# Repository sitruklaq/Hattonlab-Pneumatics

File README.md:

# 1. Overview
This system is designed to control multi-channel pneumatic smart surfaces using only small amounts of air. The pneumatic system consists of 8 independent pneumatic channels that can access positive, negative, and neutral (exhaust) states. For a smaller, portable setup, please refer to this respository: https://github.com/sitruklaq/Mini-Pneumatics

## 1.1 Table of Contents
* [1\. Overview](#1-overview)
  * [1\.1 Table of Contents](#11-table-of-contents)
* [2\. Components &amp; Pneumatic Logic](#2-components--pneumatic-logic)
* [3\. Instrument Control](#3-instrument-control)
  * [3\.1 Serial Command List](#31-serial-command-list)
    * [3\.1\.1 Valve Control](#311-valve-control)
    * [3\.1\.2 Reservoir Setpoints](#312-reservoir-setpoints)
    * [3\.1\.3 Pressure Readings](#313-pressure-readings)
* [4\. Visual Control App](#4-visual-control-app)
* [5\. Setpoint Pressure Control](#5-setpoint-pressure-control)
* [6\. Electrical Circuitry](#6-electrical-circuitry)
  * [6\.1 Electrical Components](#61-electrical-components)
  * [6\.2 PCBs](#62-pcbs)
    * [6\.2\.2 Input Valve PCB](#622-input-valve-pcb)
    * [6\.2\.3 Output Valve PCB](#623-output-valve-pcb)
    * [6\.2\.4 2 Sensor Board](#624-2-sensor-board)
[TOC]
# 2. Components & Pneumatic Logic

The instrument is designed to provide 3 pressure 'input' states: positive (+∆P), negative, (-∆P), and neutral (0∆P). Postive and negative pressures are generated through pneumatic pumps and held in reservoirs. The pressure for each reservoir is defined by the user and monitored through in-line pressure sensors. Pneumatic valves can be toggled to open and enter a common pressure line which can be accessed by independent valves that lead to channels (N=8). 

The valves are rated for +-100kPa while the pumps are generally able to reach ~+-60kPa. Valve response time is <5ms.

# 3. Instrument Control

An Arduino microncontroller is responsible for opening and closing the pneumatic valves in addition to regulating pressure setpoints of the reservoirs. 

This instrument is controlled through a Serial Connection to a computer. 

Communication to the microcontroller is accomplished through serial communication. Commands for valve control, setpoint, and pressure value requests are available in the X section.

A MATLAB GUI app uses these commands to visually control the pneumatics.

screenshot to be added later.

## 3.1 Serial Command List

The Arduino is listening for serial commands in the following structure ‘< command, optional modifier, optional modifier>’.

### 3.1.1 Valve Control

| Command Syntax | Description                                                  | Example                                 |
| :------------: | ------------------------------------------------------------ | --------------------------------------- |
|     **VO**     | **VALVE OUTPUT** Changes the state of a single output valve. <command, valve # (0-7), valve state (0-closed 1-open)> | <VO, 4, 1> opens the fifth output valve |
|     **VI**     | **VALVE INPUT**Changes the state of a single input valve. <command, valve # (0-7), valve state (0-off 1-on)> | <VO, 4, 1> opens the fifth output valve |
|    **AIV**     | **ALL INPUT VALVES** Changes the state of all input valves <command, 0/1> | <AIV,1> opens all input valves          |
|    **AOV**     | **ALL OUTPUT VALVES** Changes the state of all outpu valves <command, 0/1> | <AOV, 0> turns off all output valves    |

### 3.1.2 Reservoir Setpoints

| Command Syntax | Description                                                  | Example    |
| :------------: | ------------------------------------------------------------ | ---------- |
|    **PSP**     | Changes setpoint of positive pressure reservoir              | <PSP, 15>  |
|    **NSP**     | Changes setpoint of negative pressure reservoir              | <NSP, -15> |
|    **PVN**     | **PRESSURE VALUE NEGATIVE** prints the pressure value of the negative pressure reservoir | <PVN>      |
|    **PVO**     | **PRESSURE VALUE OUTPUT** prints the pressure value of an output pressure channel | <PVO, 3>   |
|    **PVP**     | **PRESSURE VALUE POSITIVE** prints the pressure value of the positive pressure reservoir | <PVP>      |

### 3.1.3 Pressure Readings

| Command Syntax | Description                                                  | Example  |
| :------------: | ------------------------------------------------------------ | :------: |
|      PVP       | **PRESSURE VALUE POSITIVE** prints the pressure value of the positive pressure reservoir |  <PVP>   |
|      PVN       | **PRESSURE VALUE NEGATIVE** prints the pressure value of the negative pressure reservoir |  <PVN>   |
|      PVO       | **PRESSURE VALUE OUTPUT** prints the pressure value of an output pressure channel | <PVO, 3> |

# 4. Visual Control App

A visual control app was designed using Matlab App Designer. The app is basic in functionality but is able to control valves through sending serial commands. 

# 5. Setpoint Pressure Control

Reservoir pressure is controlled by simple state monitoring. The pressure sensors monitor the pressure and the pump is turned on if the pressure drops below the Setpoint (with a small threshold).

# 6. Electrical Circuitry

## 6.1 Electrical Components

Power is supplied by an off board 12V 5A brick-style switching power supply. The 12V power is then split and one side is stepped down to 5V. The valves run on the 5V rail and are toggled through npn transistors powered by an Arduino.

**12V**

- Pumps
- Motor Controller

**5V**

- Valves

**5V (Computer-> Arduino)**

- pressure sensors
- transistors
- leds

## 6.2 PCBs

### 6.2.2 Input Valve PCB

### 6.2.3 Output Valve PCB

### 6.2.4 2 Sensor Board

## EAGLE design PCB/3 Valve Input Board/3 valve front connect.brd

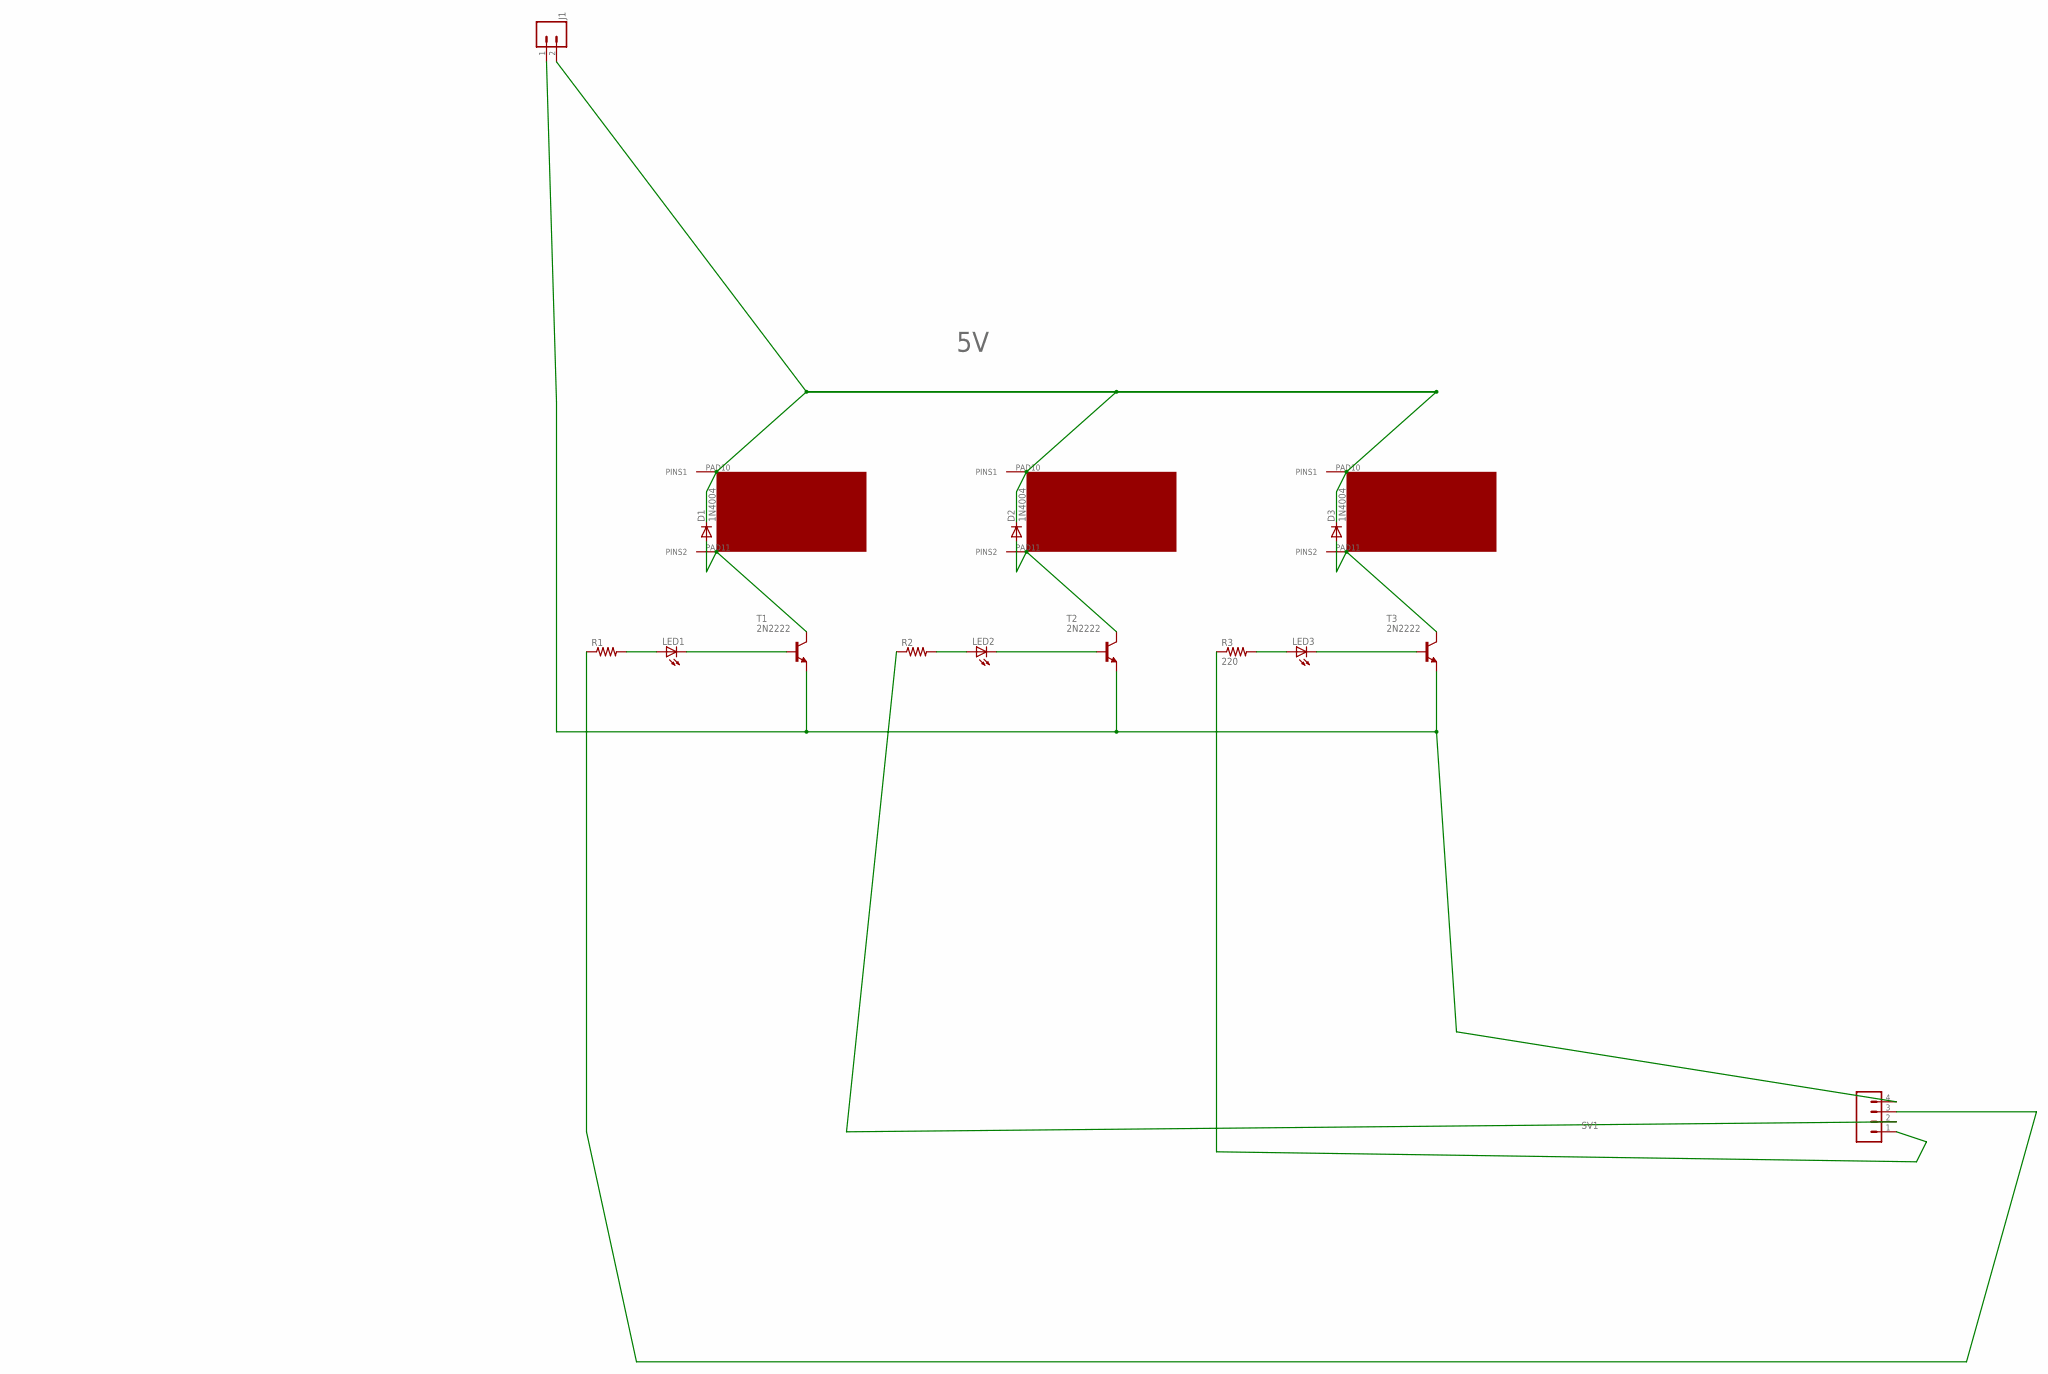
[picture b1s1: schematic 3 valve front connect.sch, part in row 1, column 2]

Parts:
D1, D2, D3: 1N4004; DO41-10
J1: CONN_023.5MM; SCREWTERMINAL-3.5MM-2
LED1, LED2, LED3: LED5MM
R1, R2: R-US_0207/10; 0207/10
R3: 220; 0207/10
SV1: CONN_04; 1X04
T1, T2, T3: 2N2222; TO92-EBC-OVAL
U$1, U$2: VALVE; VALVTEST2
VALVE3: VALVE; VALVTEST2

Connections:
5V: D1.C, D2.C, D3.C, J1.2, U$1.PAD10 (PINS1), U$2.PAD10 (PINS1), VALVE3.PAD10 (PINS1)
GND: J1.1, SV1.4, T1.E, T2.E, T3.E
unnamed: D1.A, T1.C, U$1.PAD11 (PINS2)
unnamed: LED1.K (C), T1.B
unnamed: LED1.A, R1.2
unnamed: D2.A, T2.C, U$2.PAD11 (PINS2)
unnamed: LED2.K (C), T2.B
unnamed: LED2.A, R2.2
unnamed: D3.A, T3.C, VALVE3.PAD11 (PINS2)
unnamed: LED3.K (C), T3.B
unnamed: LED3.A, R3.2
unnamed: R3.1, SV1.1
unnamed: R1.1, SV1.3
unnamed: R2.1, SV1.2

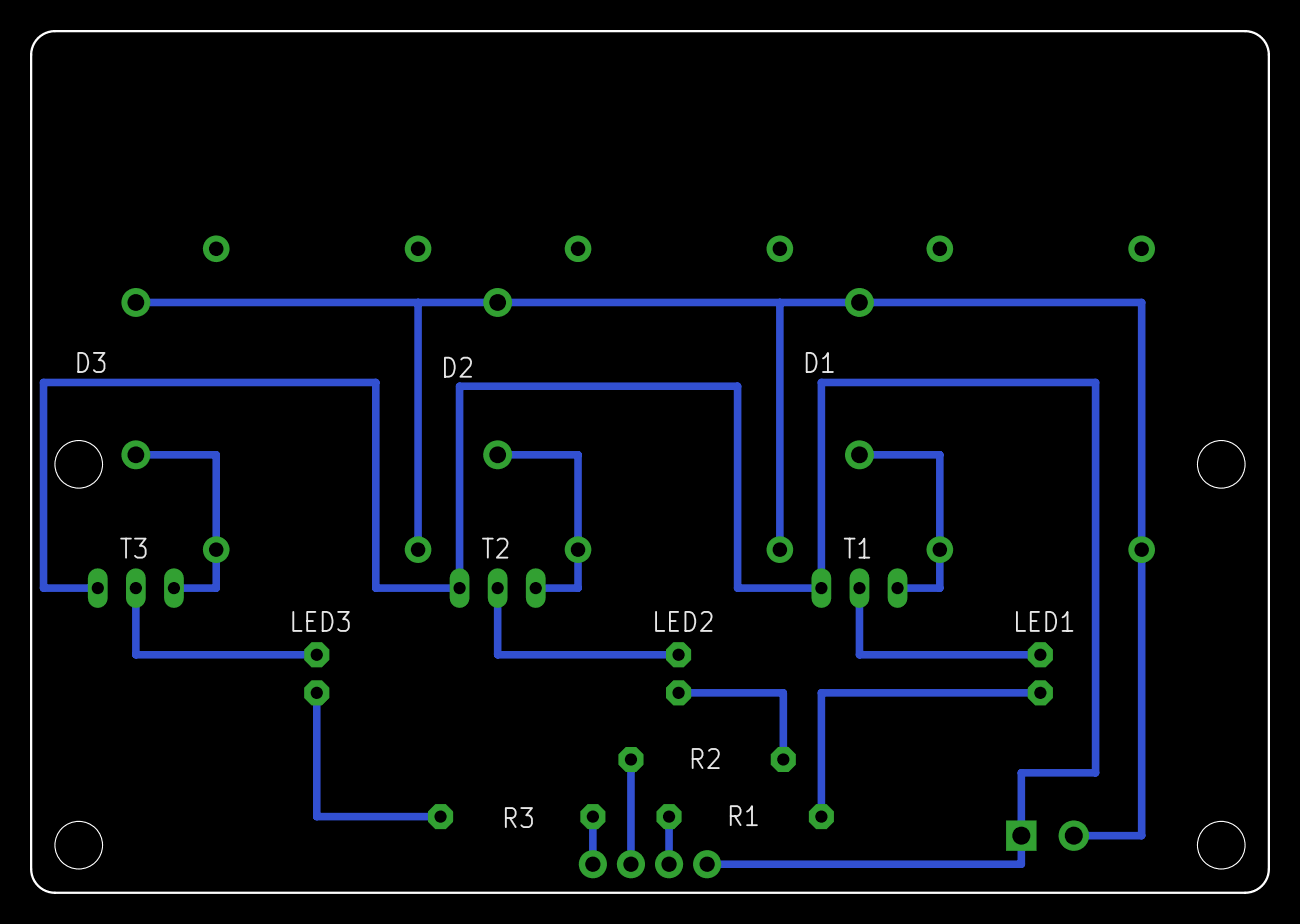
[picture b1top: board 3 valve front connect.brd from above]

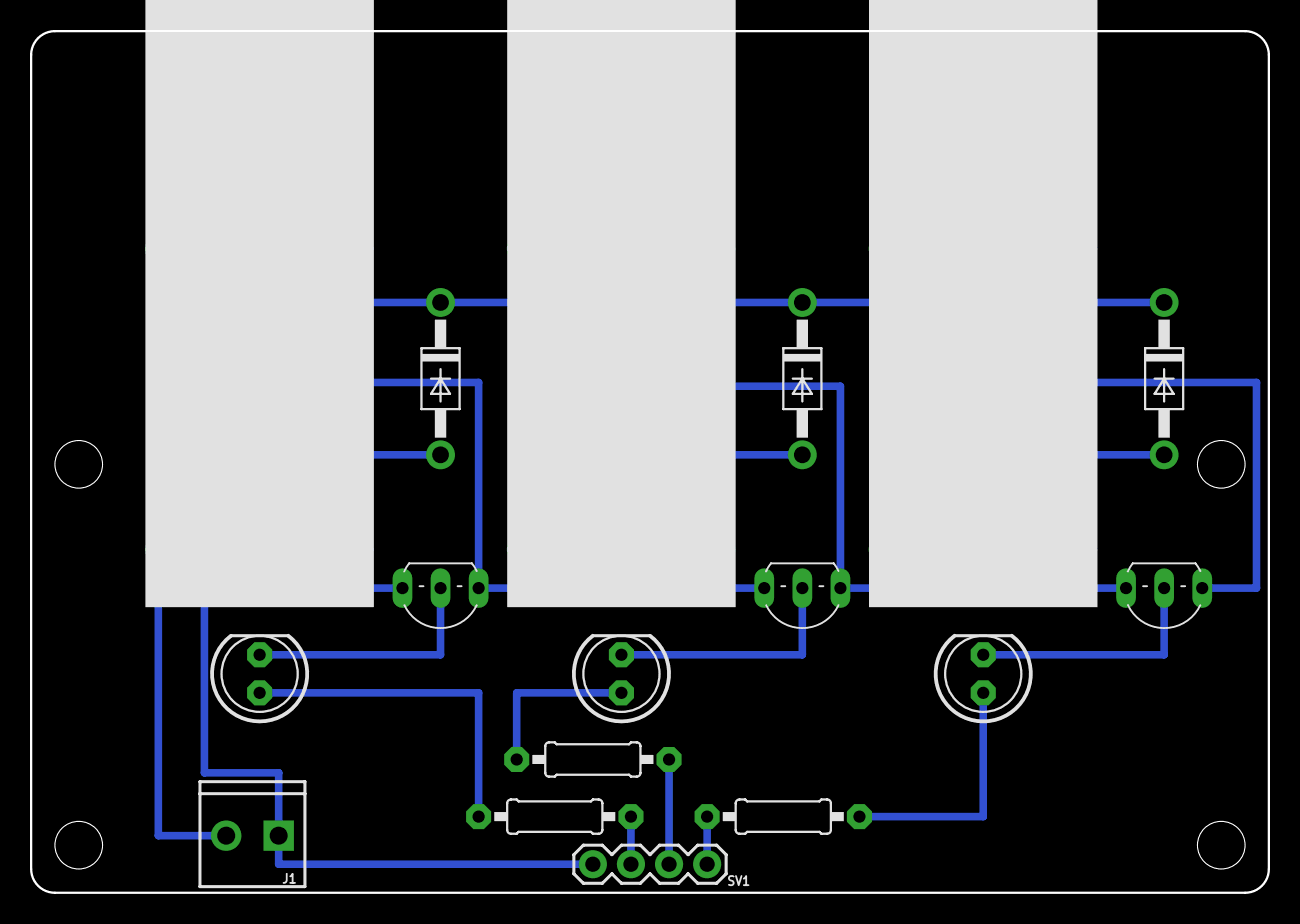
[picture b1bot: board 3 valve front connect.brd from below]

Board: 2 copper layers, 82.6 x 57.5 mm, 17 parts (17 on the bottom side), 14 nets.

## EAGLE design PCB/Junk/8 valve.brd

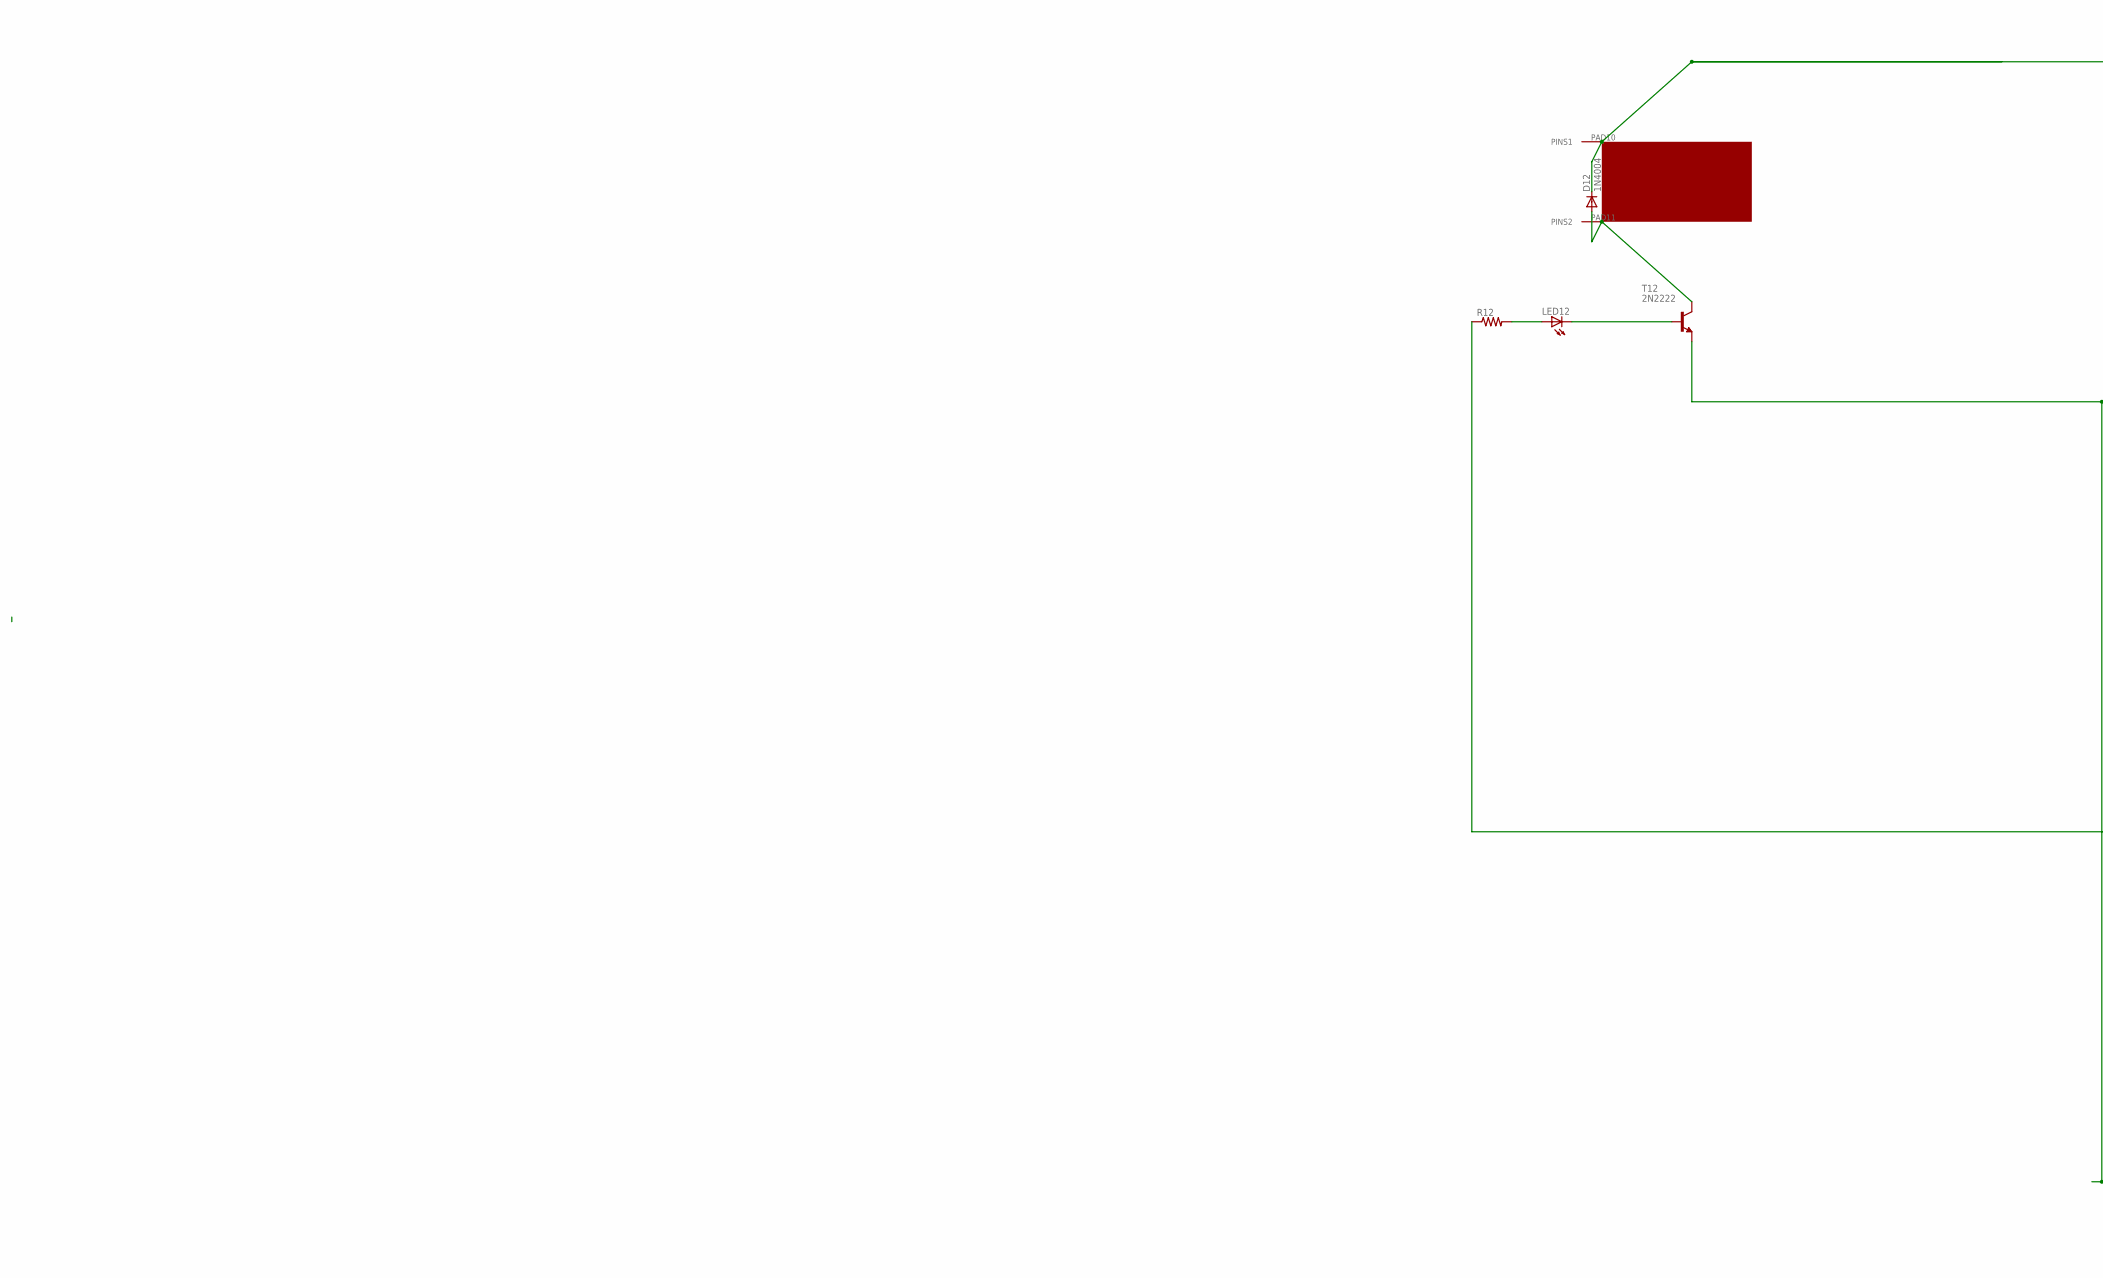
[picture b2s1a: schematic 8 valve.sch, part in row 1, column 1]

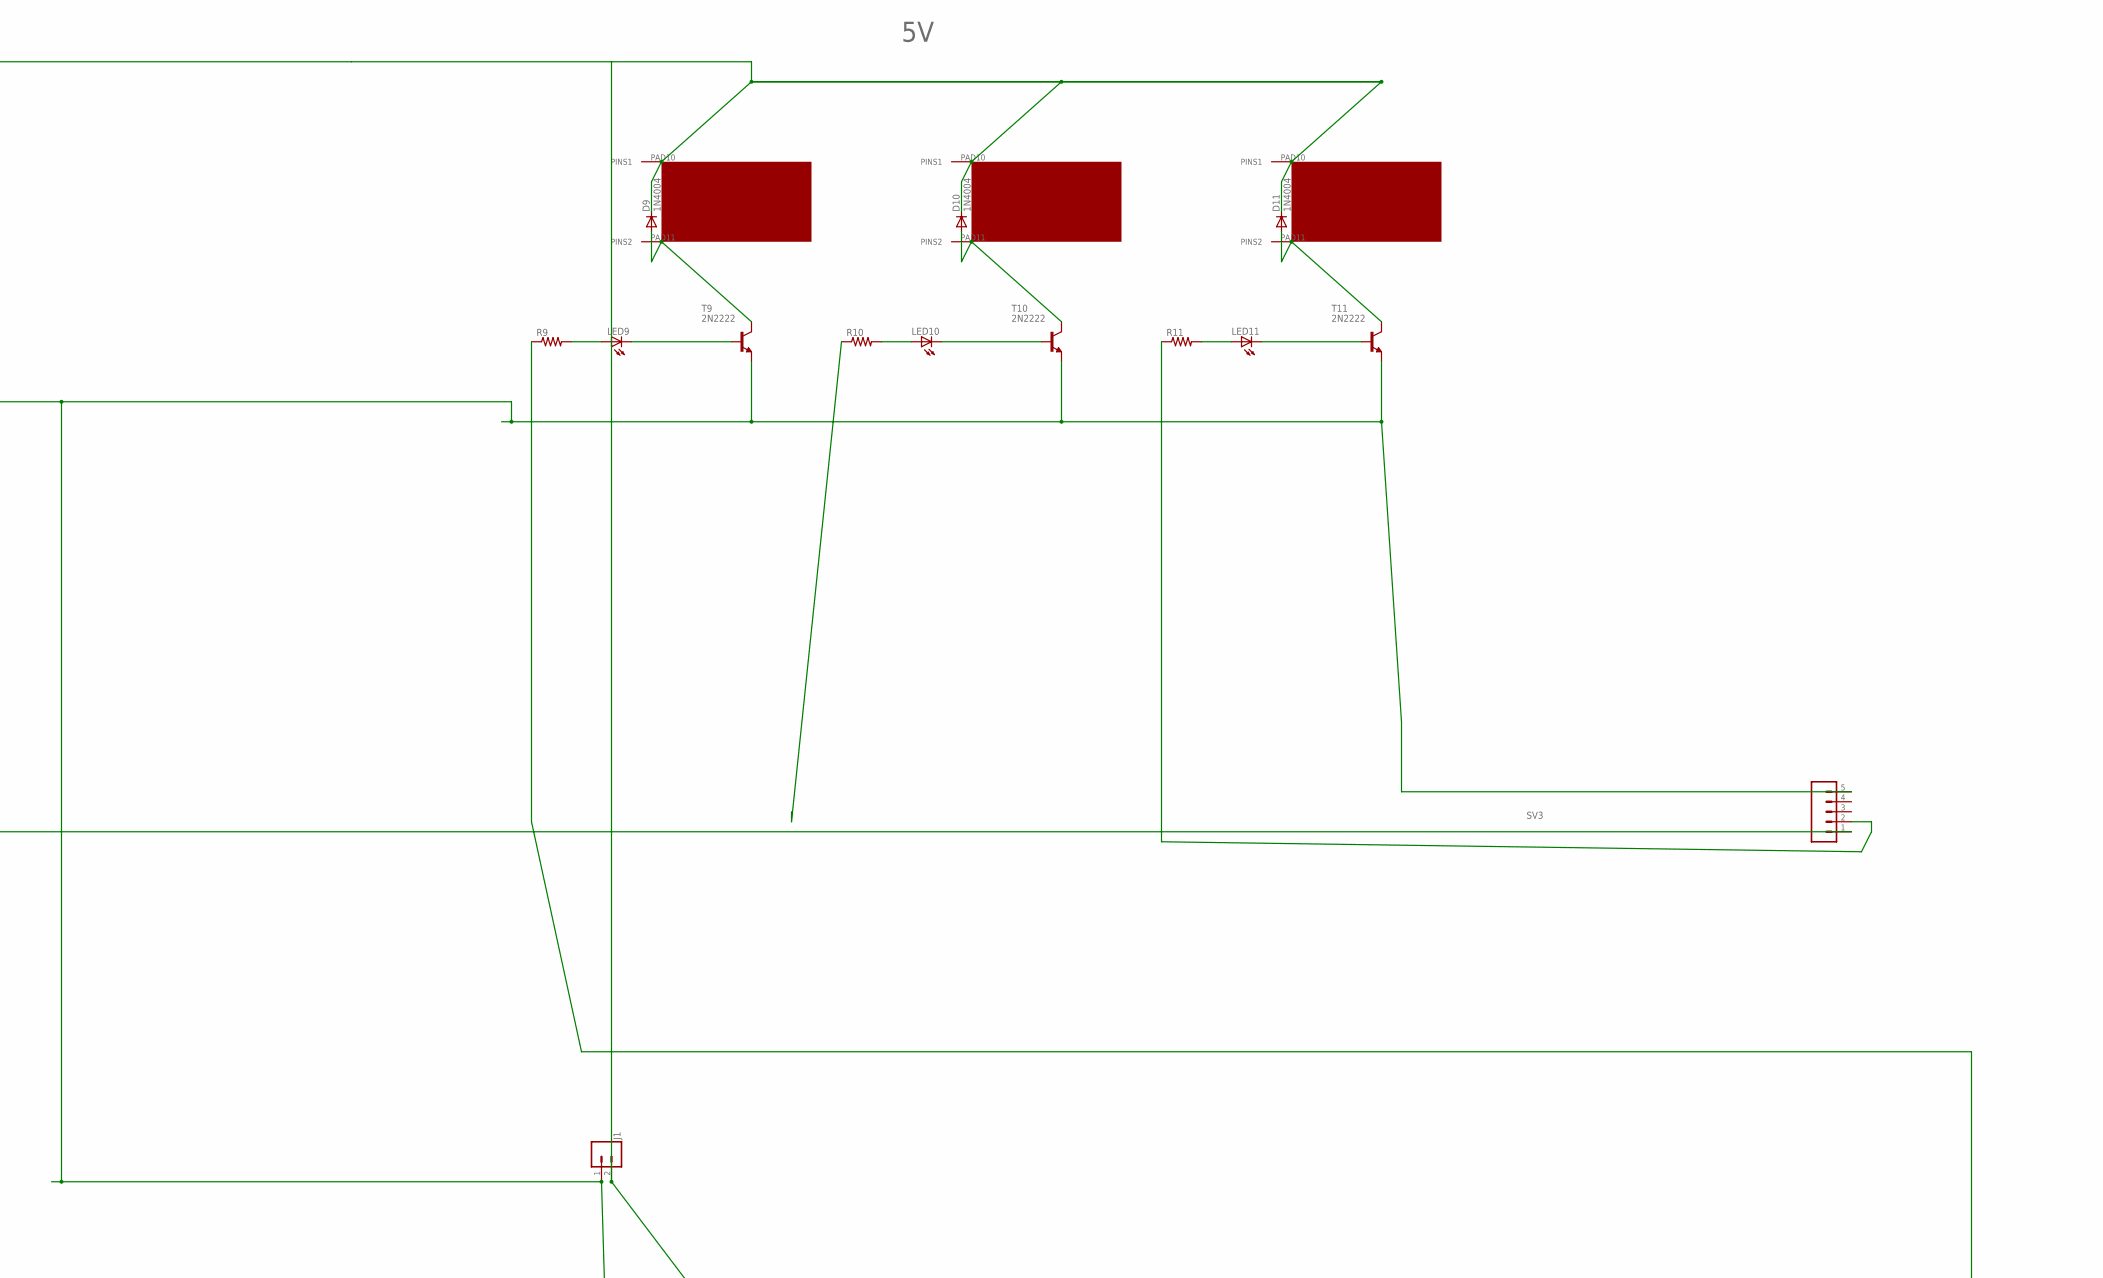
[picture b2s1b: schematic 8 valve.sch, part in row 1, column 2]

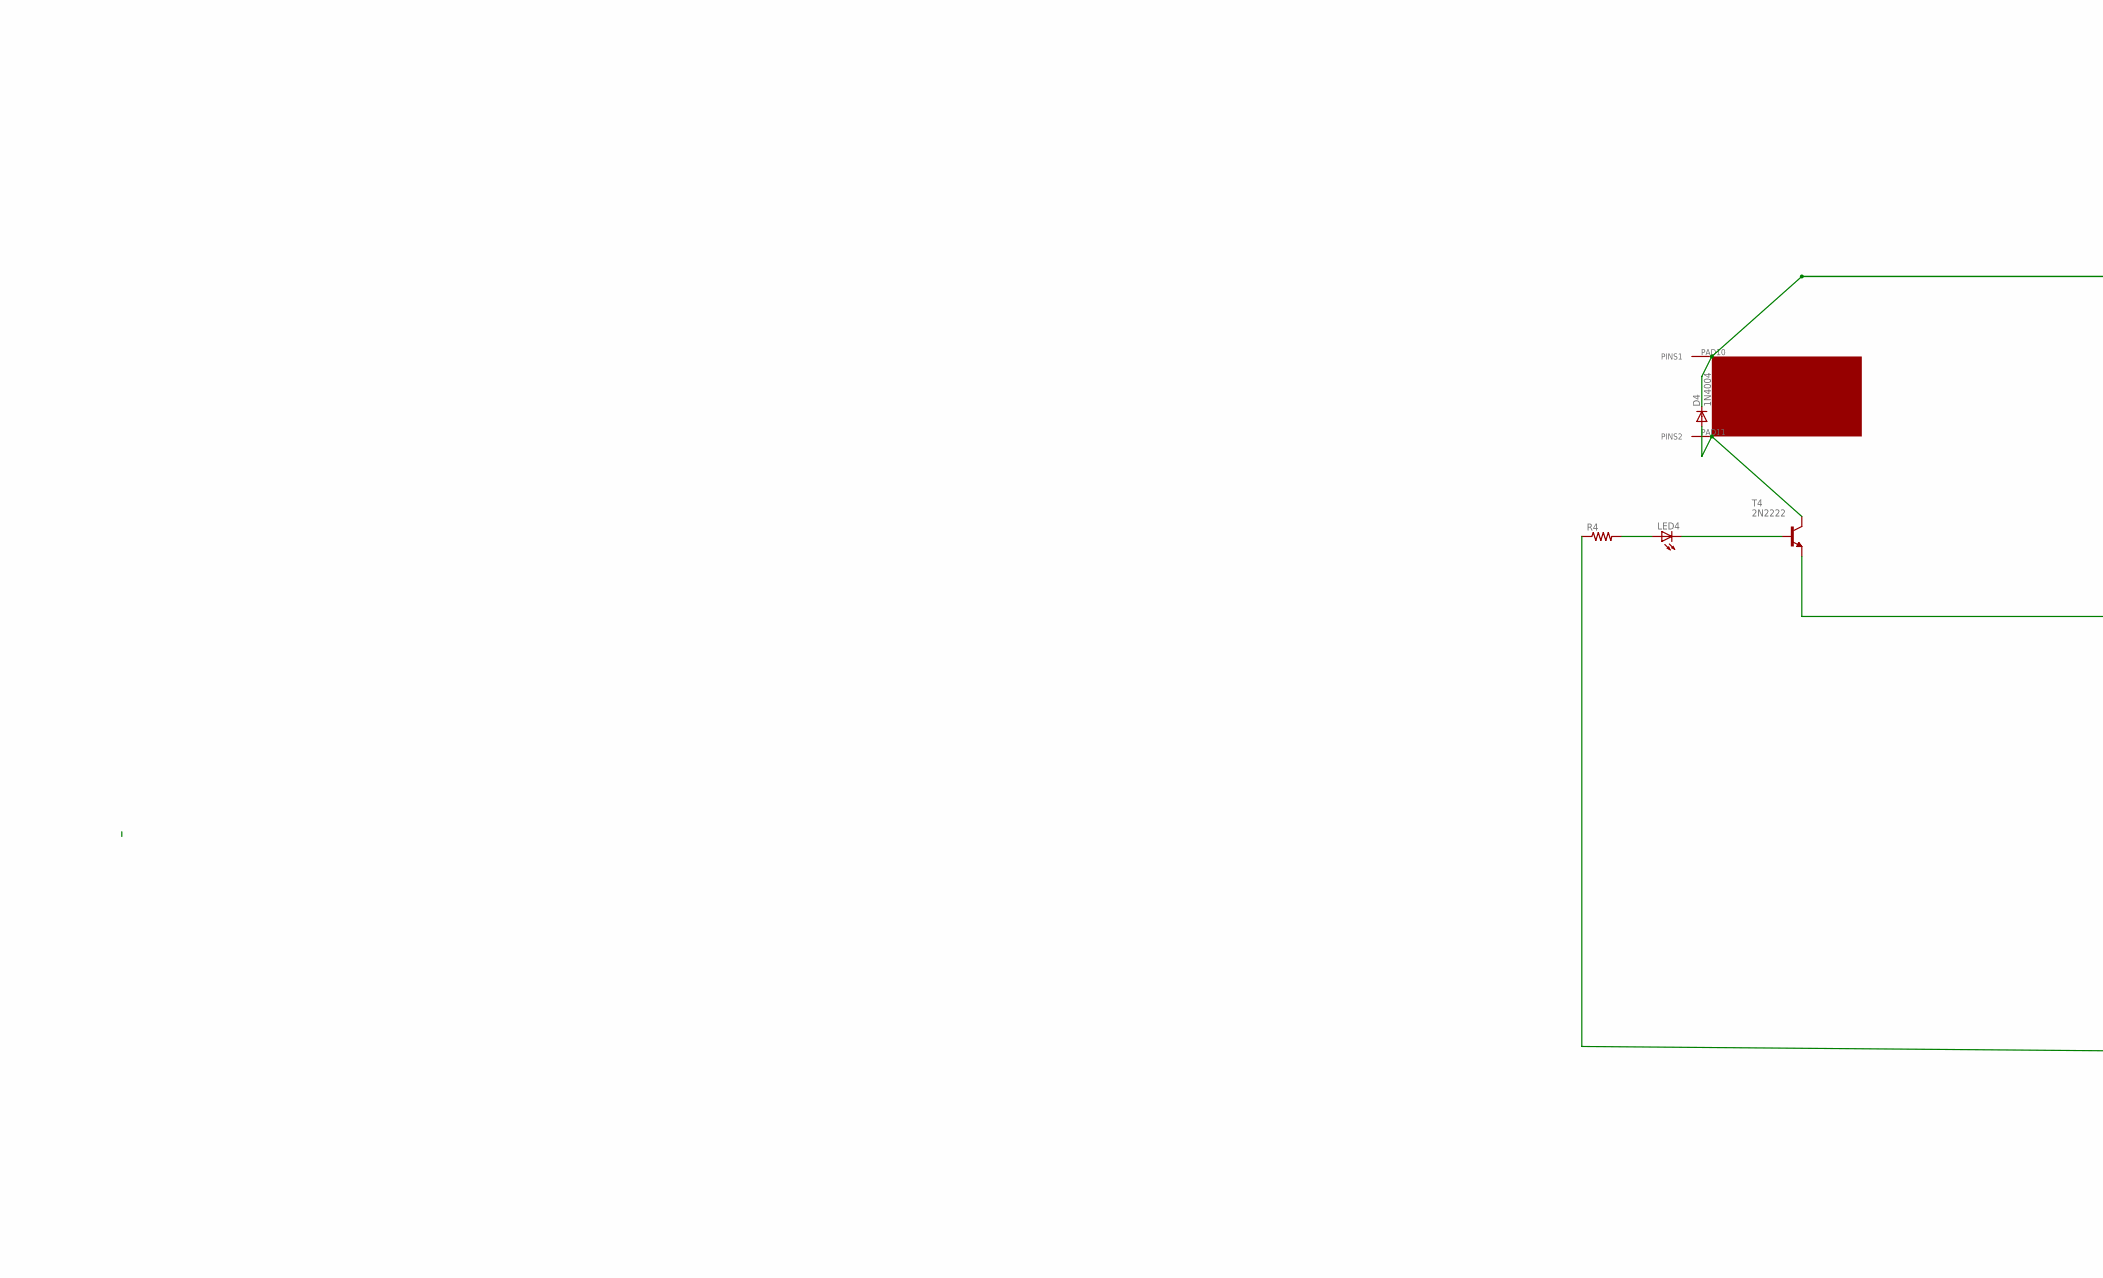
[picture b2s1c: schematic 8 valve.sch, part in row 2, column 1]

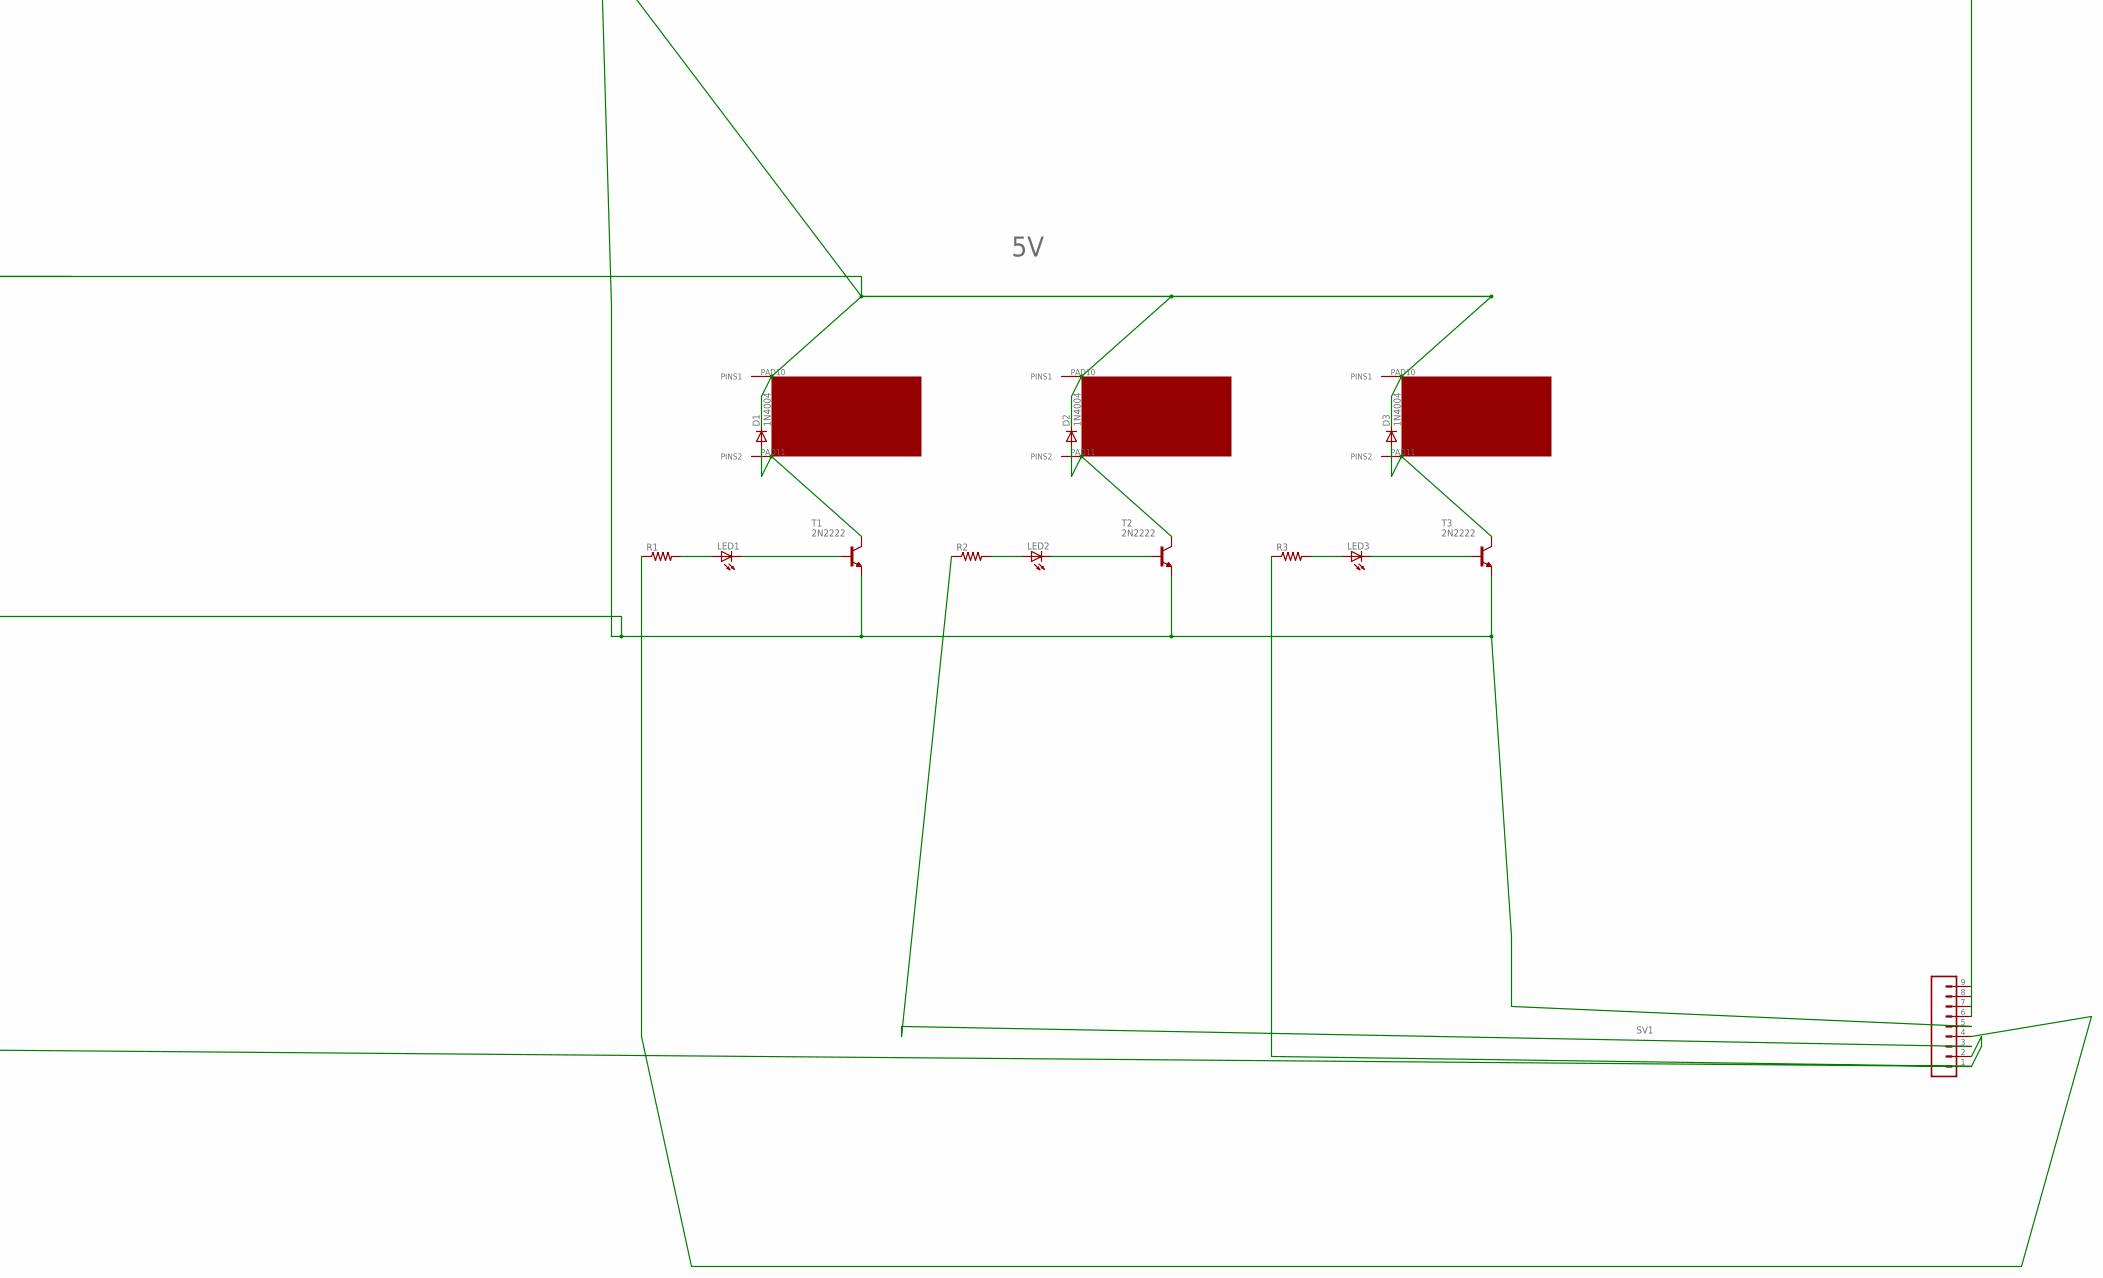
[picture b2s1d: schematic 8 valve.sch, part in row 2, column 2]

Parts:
D1, D2, D3, D4, D9, D10, D11, D12: 1N4004; DO41-10
J1: CONN_023.5MM; SCREWTERMINAL-3.5MM-2
LED1, LED2, LED3, LED4, LED9, LED10, LED11, LED12: LED5MM
R1, R2, R3, R4, R9, R10, R11, R12: R-US_0207/10; 0207/10
SV1: CONN_09; 1X09
SV3: CONN_05; 1X05
T1, T2, T3, T4, T9, T10, T11, T12: 2N2222; TO92-EBC-OVAL
U$1, U$2, U$3, U$7, U$8, U$9: VALVE; VALVTEST2
VALVE2, VALVE3: VALVE; VALVTEST2

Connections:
5V: D1.C, D2.C, D3.C, D4.C, D9.C, D10.C, D11.C, D12.C, J1.2, U$1.PAD10 (PINS1), U$2.PAD10 (PINS1), U$3.PAD10 (PINS1), U$7.PAD10 (PINS1), U$8.PAD10 (PINS1), U$9.PAD10 (PINS1), VALVE2.PAD10 (PINS1), VALVE3.PAD10 (PINS1)
GND: J1.1, SV1.5, SV3.5, T1.E, T2.E, T3.E, T4.E, T9.E, T10.E, T11.E, T12.E
unnamed: D1.A, T1.C, U$1.PAD11 (PINS2)
unnamed: LED1.K (C), T1.B
unnamed: LED1.A, R1.2
unnamed: D4.A, T4.C, U$3.PAD11 (PINS2)
unnamed: D2.A, T2.C, U$2.PAD11 (PINS2)
unnamed: LED2.K (C), T2.B
unnamed: LED2.A, R2.2
unnamed: LED4.K (C), T4.B
unnamed: D3.A, T3.C, VALVE3.PAD11 (PINS2)
unnamed: LED3.K (C), T3.B
unnamed: LED3.A, R3.2
unnamed: LED4.A, R4.2
unnamed: R4.1, SV1.1
unnamed: R2.1, SV1.3
unnamed: R12.1, SV3.1
unnamed: R3.1, SV1.2
unnamed: R9.1, SV1.6
unnamed: R1.1, SV1.4
unnamed: D9.A, T9.C, U$7.PAD11 (PINS2)
unnamed: LED9.K (C), T9.B
unnamed: LED9.A, R9.2
unnamed: D10.A, T10.C, U$8.PAD11 (PINS2)
unnamed: LED10.K (C), T10.B
unnamed: LED10.A, R10.2
unnamed: D11.A, T11.C, VALVE2.PAD11 (PINS2)
unnamed: LED11.K (C), T11.B
unnamed: LED11.A, R11.2
unnamed: R11.1, SV3.2
unnamed: D12.A, T12.C, U$9.PAD11 (PINS2)
unnamed: LED12.K (C), T12.B
unnamed: LED12.A, R12.2

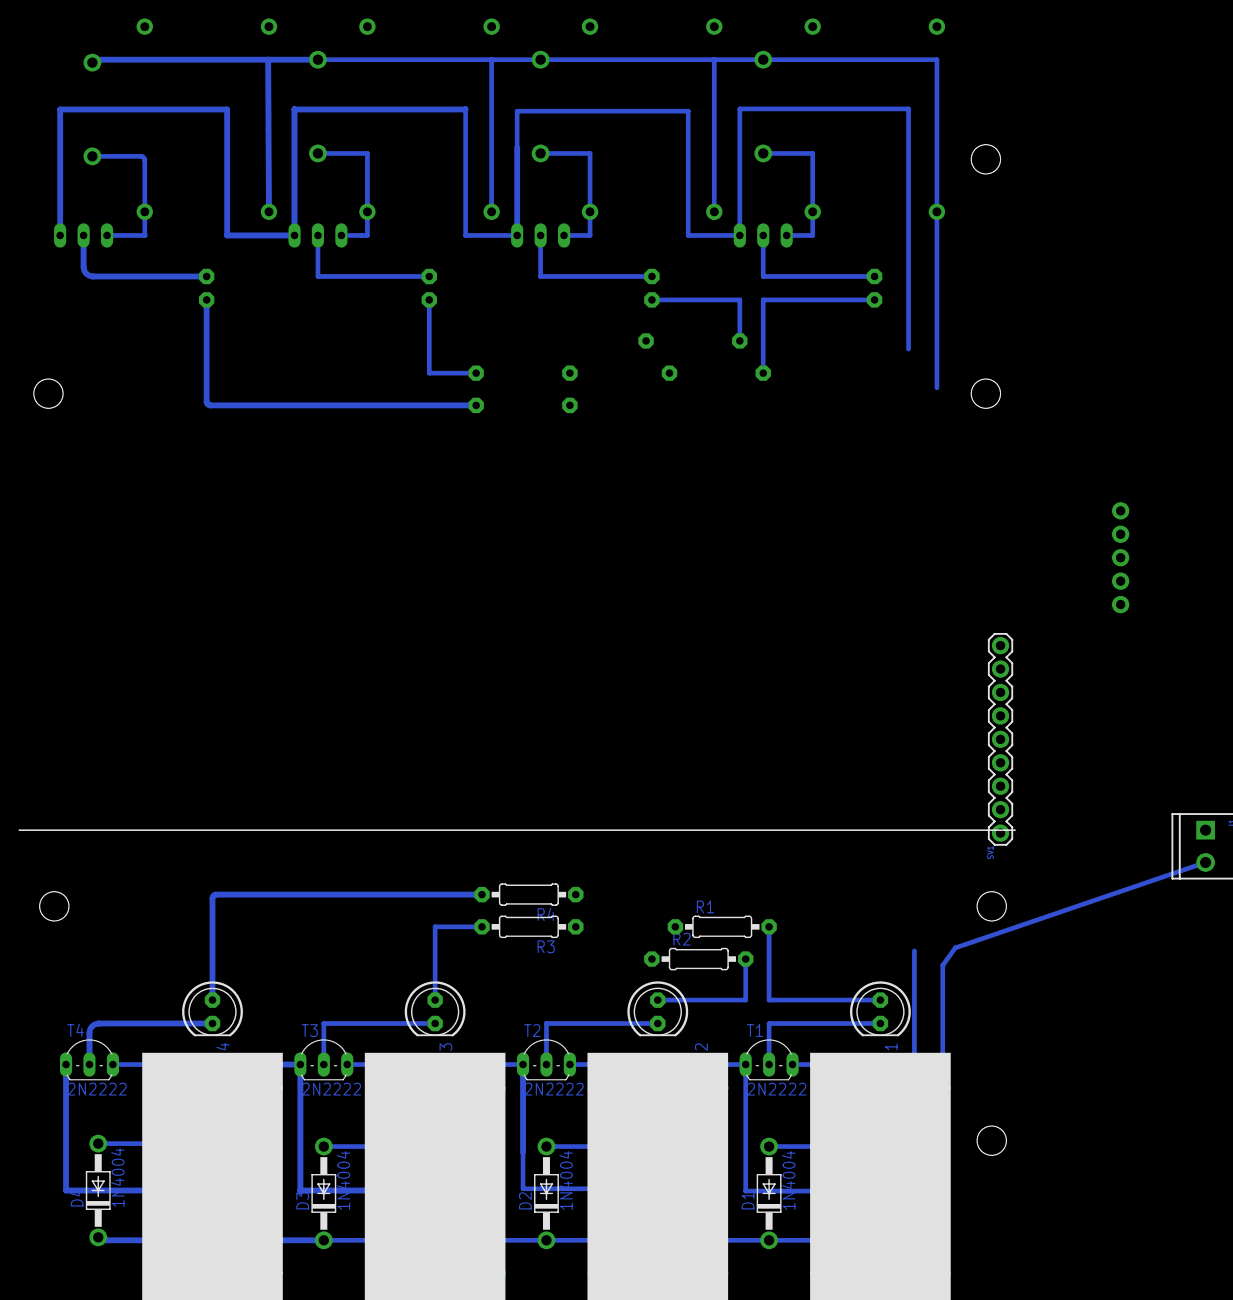
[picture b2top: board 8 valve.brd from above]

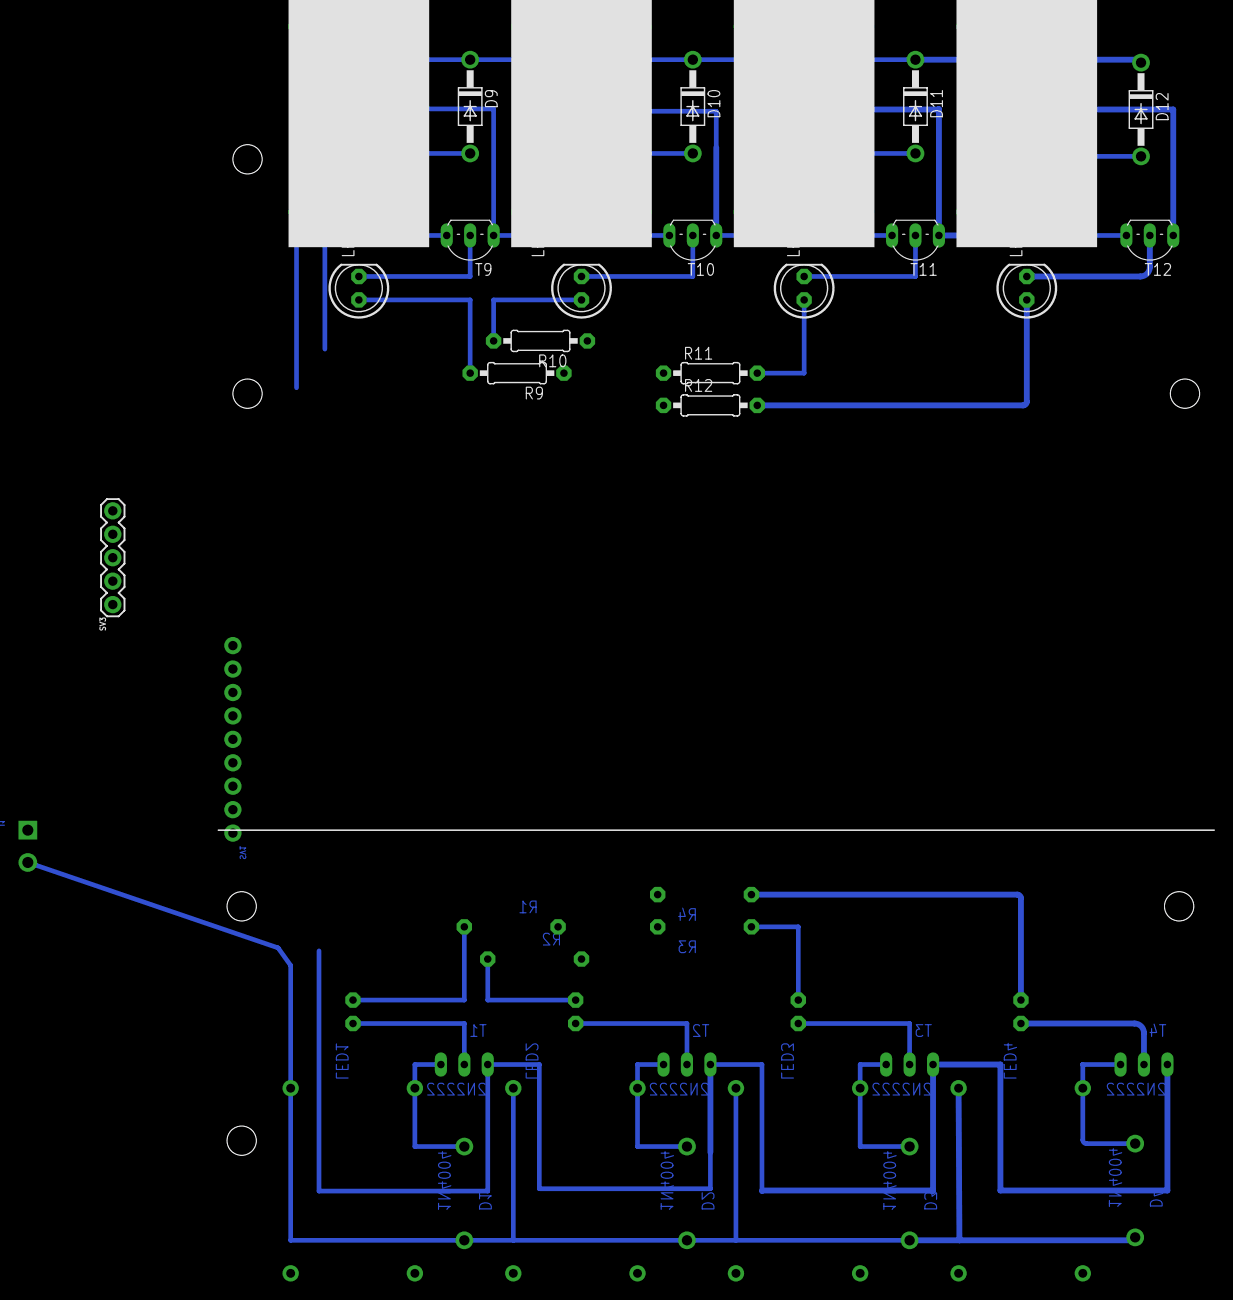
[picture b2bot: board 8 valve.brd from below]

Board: 2 copper layers, 43 parts (21 on the bottom side), 33 nets.

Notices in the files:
parts and their libraries:
SparkFun-Connectors: Licensing: Creative Commons ShareAlike 4.0 International - https://creativecommons.org/licenses/by-sa/4.0
